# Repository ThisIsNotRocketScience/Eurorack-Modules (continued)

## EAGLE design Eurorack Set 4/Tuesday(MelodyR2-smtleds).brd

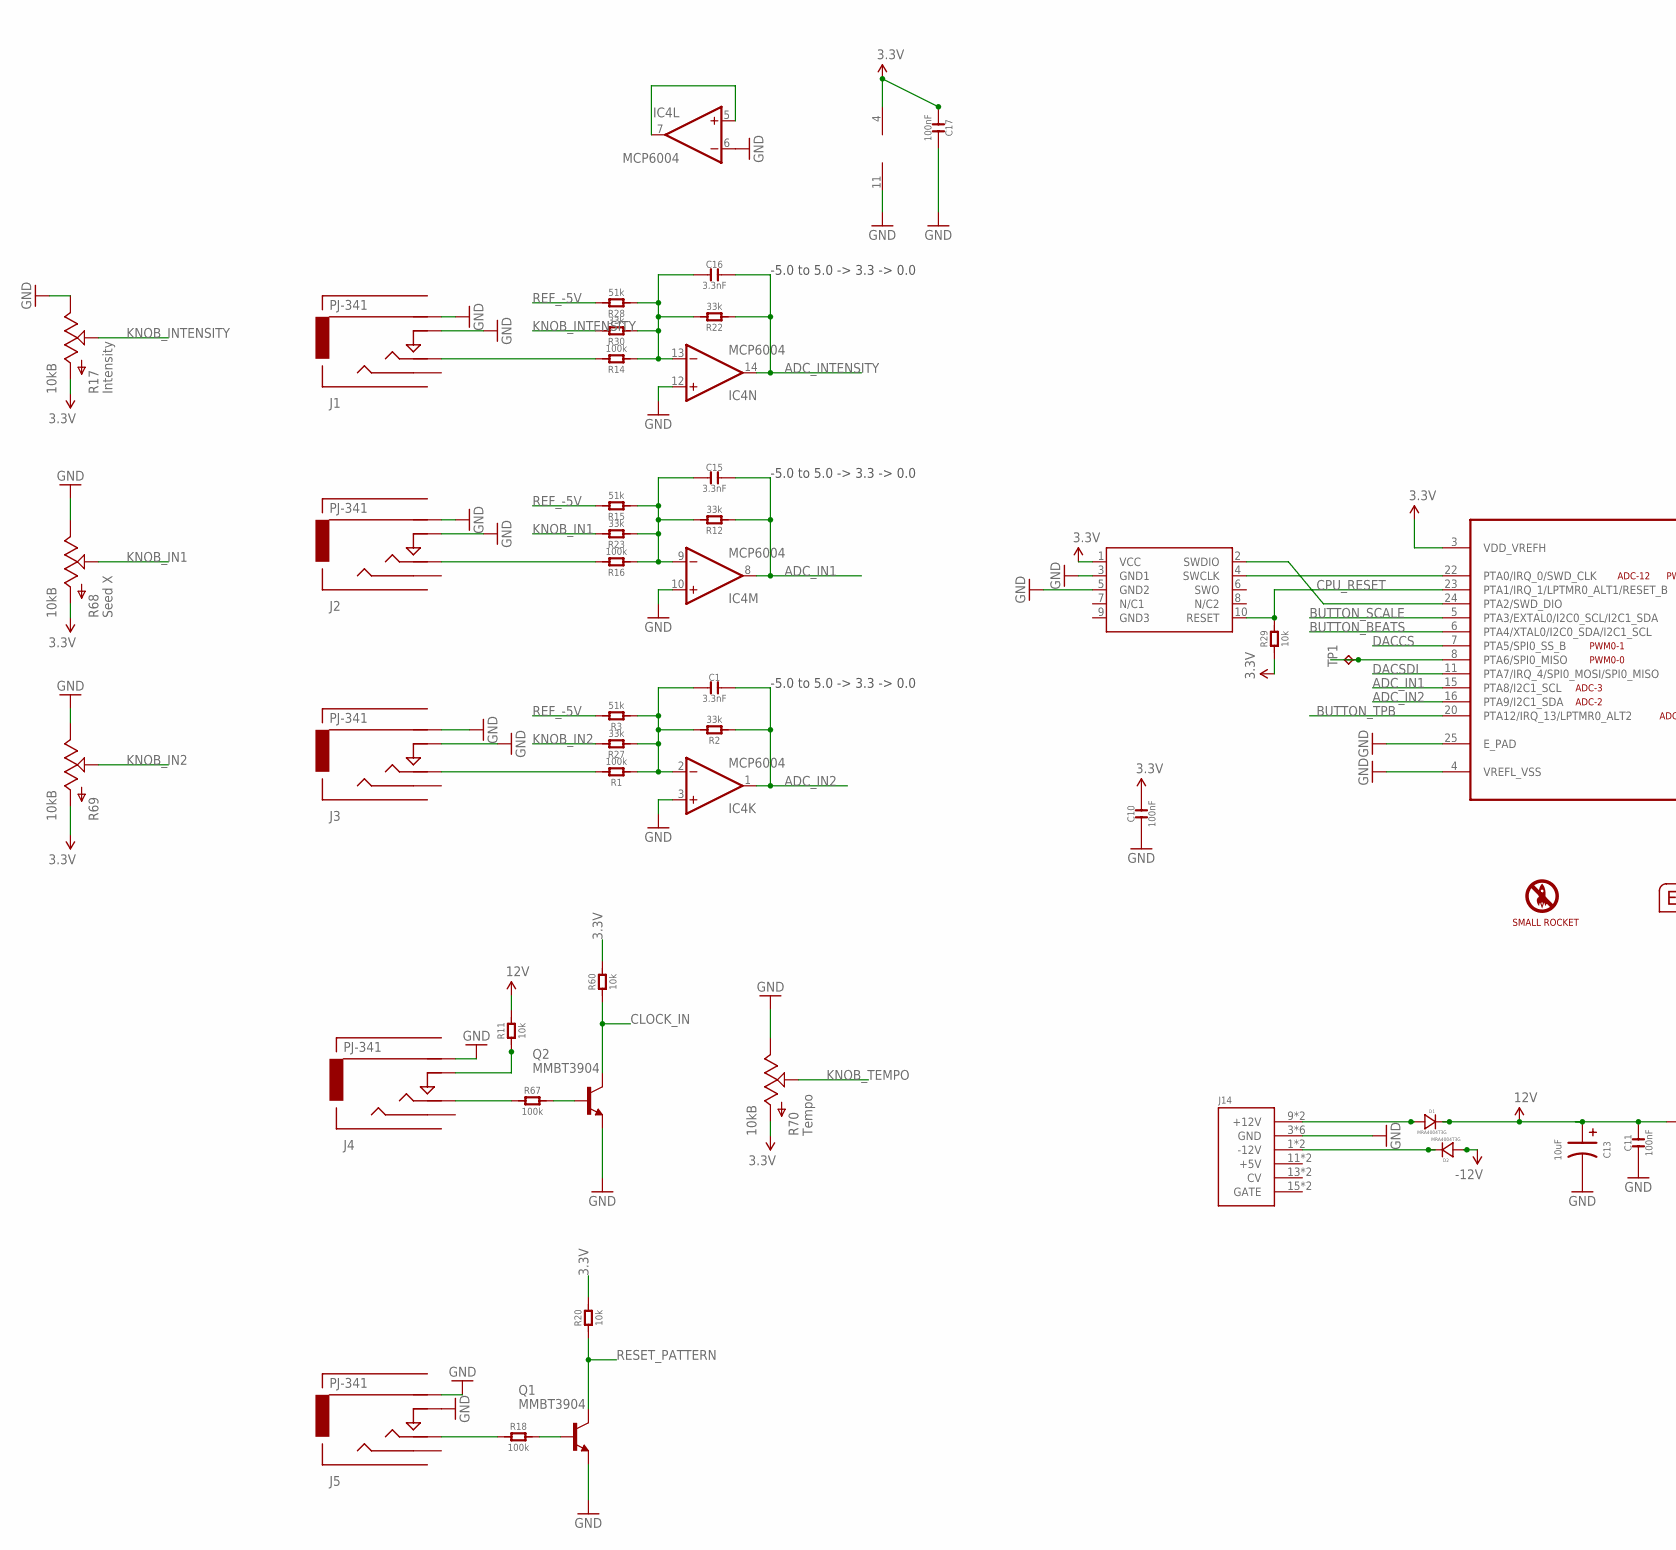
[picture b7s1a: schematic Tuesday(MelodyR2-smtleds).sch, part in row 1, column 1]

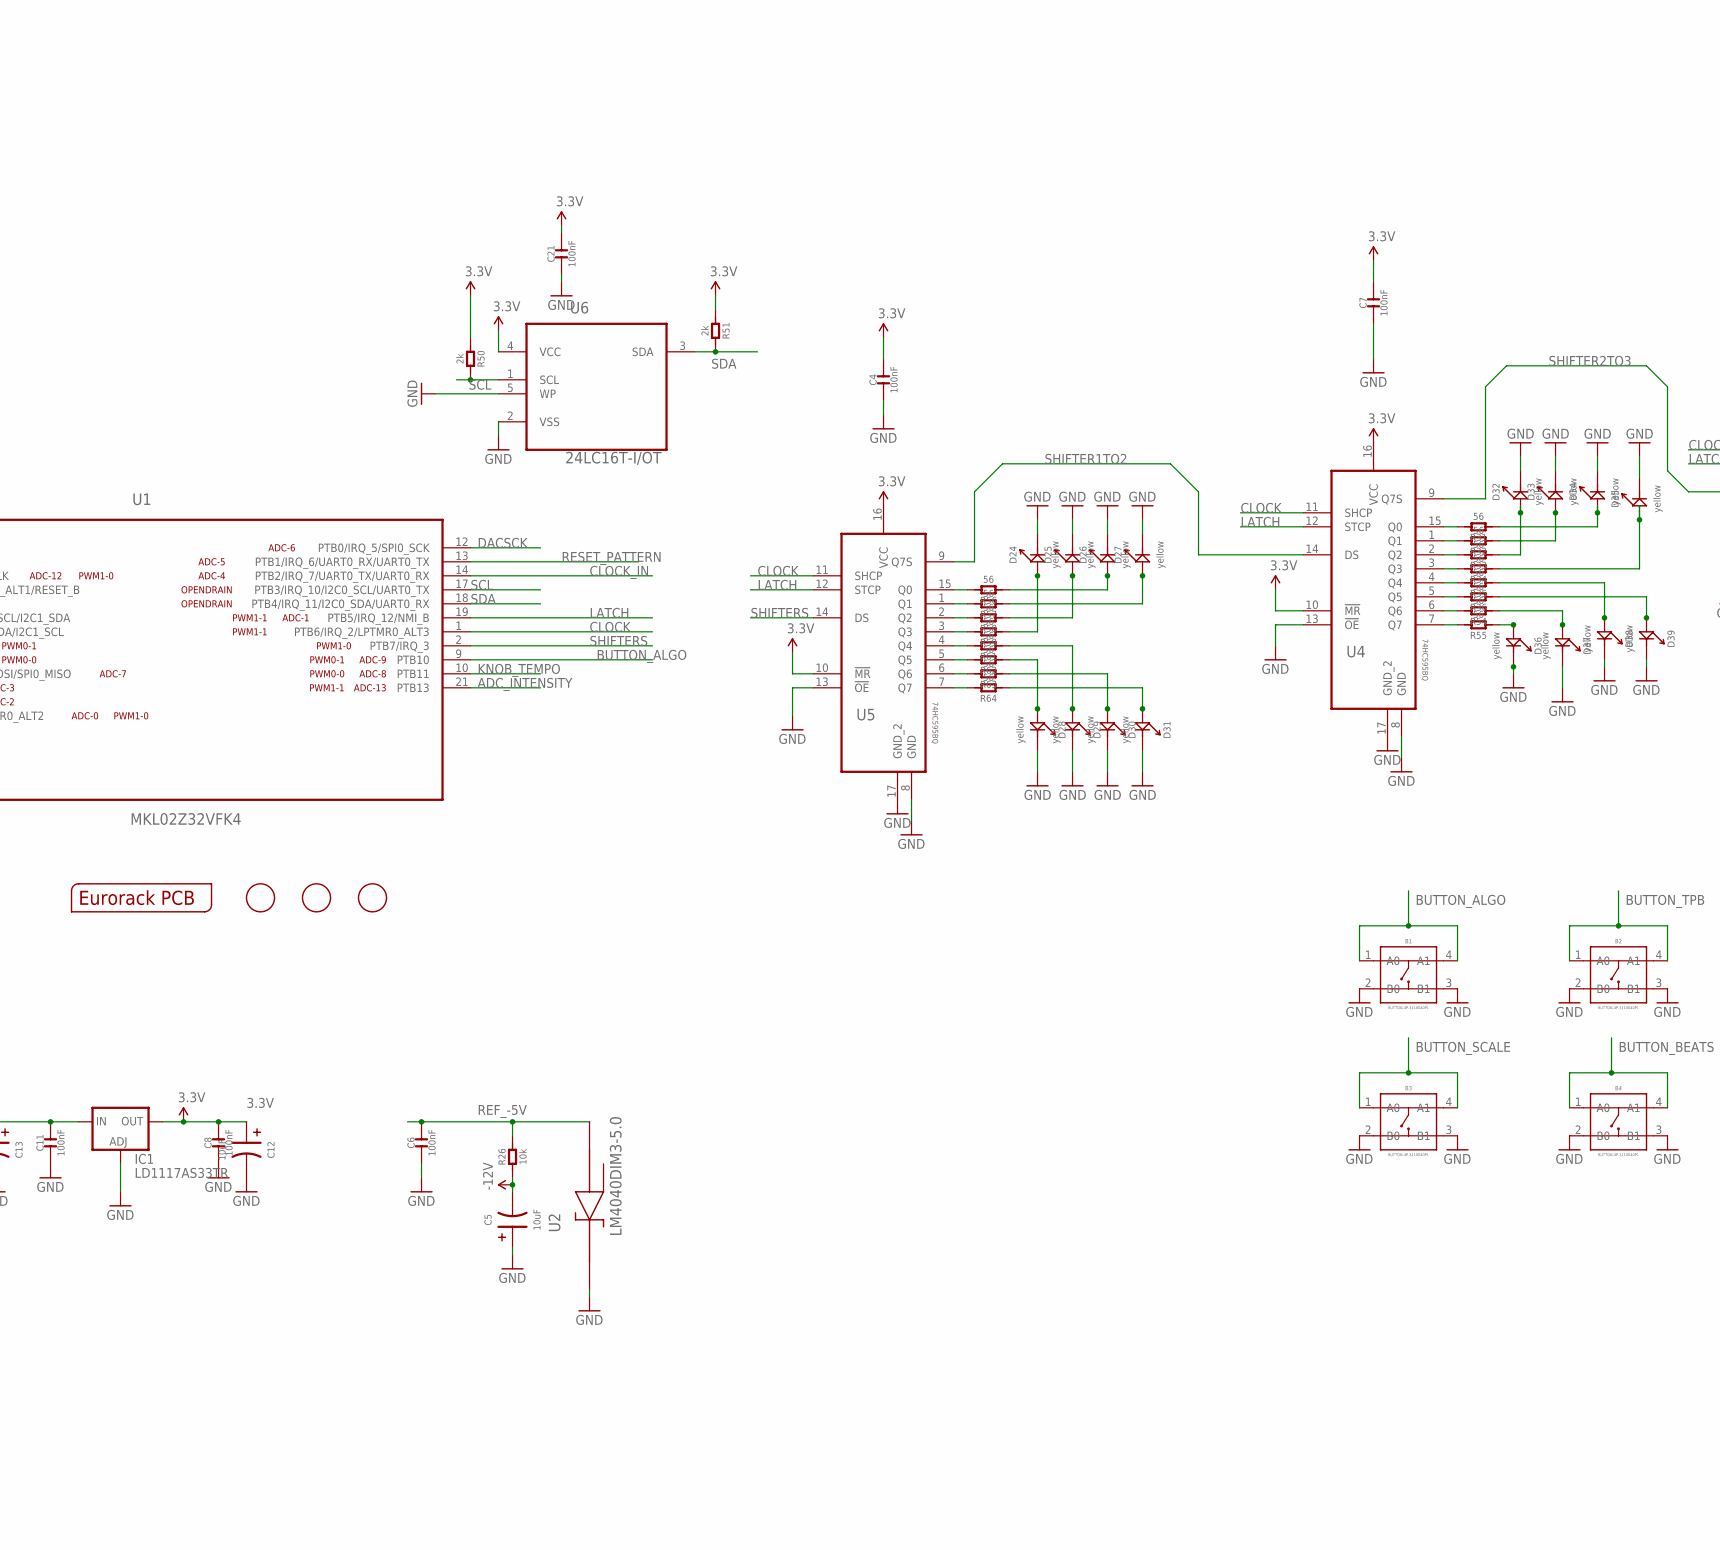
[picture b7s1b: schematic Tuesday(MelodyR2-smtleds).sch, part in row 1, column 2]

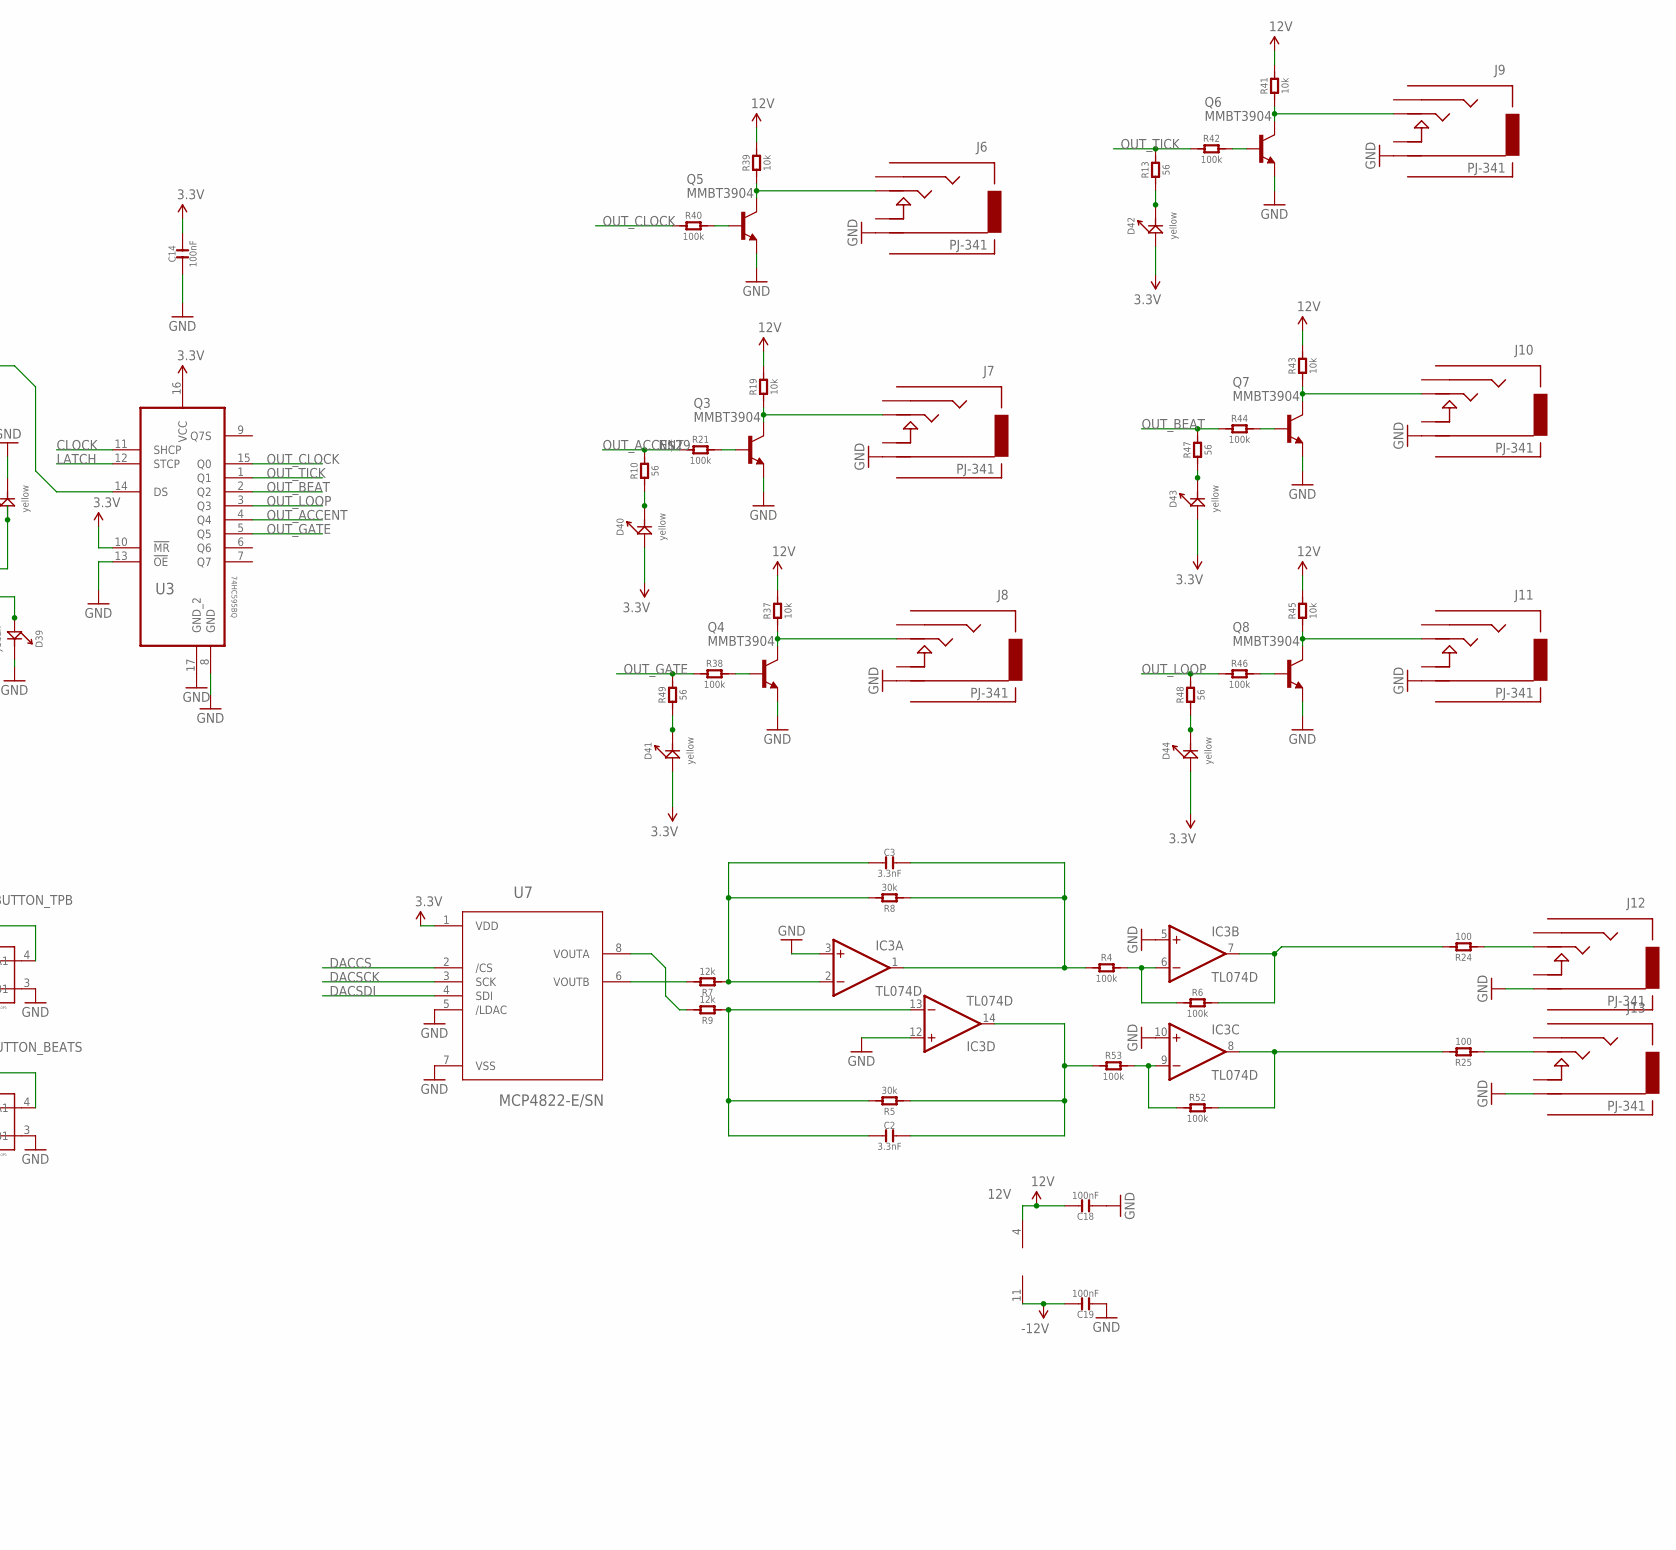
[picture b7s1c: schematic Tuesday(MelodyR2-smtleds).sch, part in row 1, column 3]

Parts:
B1, B2, B3, B4: BUTTON-4P-3110040P1; 4P-6.0X6.0X5.0H
C1, C2, C3, C15, C16: 3.3nF; C0603
C4, C7, C8, C10, C11, C14, C17, C18, C19, C21: 100nF; C0603; MPN MC0603F104Z160CT
C5, C12, C13: 10uF; AVX-A; MPN TAJB106K020RNJ
C6: 100nF; C0603; MPN 06035C104KAT2A
D1, D2: MRA4004T3G; DO-214AC; MPN US1G-E3/5AT
D24, D25, D26, D27, D28, D29, D30, D31, D32, D33, D34, D35, D36, D37, D38, D39, D40, D41, D42, D43, D44: yellow; LED0603
FID1, FID2, FID3: FIDUCIAL; FIDUCIAL_1MM
IC1: LD1117AS33TR; SOT223; MPN LD1117AS33TR
IC3: TL074D; SO14; MPN TL074CD
IC4: MCP6004; SO14; MPN MCP6004-I/SL.
J1, J2, J3, J4, J5: PJ-341; 3.5MM-JACK-SWITCH-13MM-INPUT
J6, J7, J8, J9, J10, J11, J12, J13: PJ-341; 3.5MM-JACK-SWITCH-13MM-OUTPUT
J14: POWER; POWER_16
OUTLINE: EURORACK_PCB12HP; EURORACK12HPPCB
PRETTY1: SMALLROCKET
Q1, Q2, Q3, Q4, Q5, Q6, Q7, Q8: MMBT3904; SOT23-BEC; MPN PMBT3904,215
R1, R4, R6, R14, R16, R18, R21, R38, R40, R42, R44, R46, R52, R53, R67: 100k; R0603
R2, R12, R22, R23, R27, R30: 33k; R0603
R3, R15, R28: 51k; R0603
R5, R8: 30k; R0603
R7, R9: 12k; R0603
R10, R13, R31, R32, R33, R34, R35, R36, R47, R48, R49, R54, R55, R56, R57, R58, R59, R61, R62, R63, R64: 56; R0603
R11, R19, R20, R26, R29, R37, R39, R41, R43, R45, R60: 10k; R0603
R17, R68, R69, R70: 10kB; OG-POTS_ALPS_POT_VERTICAL
R24, R25: 100; R0603
R50, R51: 2k; R0603
SWD1: CORTEX_SWD; M50-3600542
TP1: TPB1,27; B1,27
U1: MKL02Z32VFK4; QFN50P400X400X100-25N
U2: LM4040DIM3-5.0; SOT95P237X112-3N
U3, U4, U5: 74HC595BQ; QFN50P250X350X100-17N
U6: 24LC16T-I/OT; SOT95P290X145-5N; MPN 24LC00T-I/OT
U7: MCP4822-E/SN; SOIC8-N_MC

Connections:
3.3V: C4.2, C7.2, C8.2, C10.2, C12.+ (1), C14.2, C17.1, C21.2, D40.+, D41.+, D42.+, D43.+, D44.+, IC1.2 (OUT), IC1.4 (OUT), IC4.4 (V+), R17.P$3 (A), R20.2, R29.1, R50.1, R51.1, R60.2, R68.P$3 (A), R69.P$3 (A), R70.P$3 (A), SWD1.1 (VCC), U1.3 (VDD_VREFH), U3.10 (!MR), U3.16 (VCC), U4.10 (!MR), U4.16 (VCC), U5.10 (!MR), U5.16 (VCC), U6.4 (VCC), U7.1 (VDD)
12V: C11.2, C13.+ (1), C18.2, D1.2 (-), IC1.3 (IN), IC3.4 (V+), R11.2, R19.2, R37.2, R39.2, R41.2, R43.2, R45.2
-12V: C5.- (2), C19.2, D2.1 (+), IC3.11 (V-), R26.1
ADC_IN1: C15.2, IC4.8 (OUT), R12.1, U1.15 (PTA8/I2C1_SCL)
ADC_IN2: C1.2, IC4.1 (OUT), R2.1, U1.16 (PTA9/I2C1_SDA)
ADC_INTENSITY: C16.2, IC4.14 (OUT), R22.1, U1.21 (PTB13)
BUTTON_ALGO: B1.1 (A0), B1.4 (A1), U1.9 (PTB10)
BUTTON_BEATS: B4.1 (A0), B4.4 (A1), U1.6 (PTA4/XTAL0/I2C0_SDA/I2C1_SCL)
BUTTON_SCALE: B3.1 (A0), B3.4 (A1), U1.5 (PTA3/EXTAL0/I2C0_SCL/I2C1_SDA)
BUTTON_TPB: B2.1 (A0), B2.4 (A1), U1.20 (PTA12/IRQ_13/LPTMR0_ALT2)
CLOCK: U1.1 (PTB6/IRQ_2/LPTMR0_ALT3), U3.11 (SHCP), U4.11 (SHCP), U5.11 (SHCP)
CLOCK_IN: Q2.C, R60.1, U1.14 (PTB2/IRQ_7/UART0_TX/UART0_RX)
CPU_RESET: R29.2, SWD1.10 (RESET), U1.23 (PTA1/IRQ_1/LPTMR0_ALT1/RESET_B)
D21: D43.-, R47.1
DACCS: U1.7 (PTA5/SPI0_SS_B), U7.2 (/CS)
DACSCK: U1.12 (PTB0/IRQ_5/SPI0_SCK), U7.3 (SCK)
DACSDI: U1.11 (PTA7/IRQ_4/SPI0_MOSI/SPI0_MISO), U7.4 (SDI)
GND: B1.2 (B0), B1.3 (B1), B2.2 (B0), B2.3 (B1), B3.2 (B0), B3.3 (B1), B4.2 (B0), B4.3 (B1), C4.1, C5.+ (1), C6.1, C7.1, C8.1, C10.1, C11.1, C12.- (2), C13.- (2), C14.1, C17.2, C18.1, C19.1, C21.1, D24.-, D25.-, D26.-, D27.-, D28.-, D29.-, D30.-, D31.-, D32.-, D33.-, D34.-, D35.-, D36.-, D37.-, D38.-, D39.-, IC1.1 (ADJ), IC3.3 (+IN), IC3.5 (+IN), IC3.10 (+IN), IC3.12 (+IN), IC4.3 (+IN), IC4.6 (-IN), IC4.10 (+IN), IC4.11 (V-), IC4.12 (+IN), J1.RING@3 (RING), J1.SWITCH@3 (SWITCH), J2.RING@3 (RING), J2.SWITCH@3 (SWITCH), J3.RING@3 (RING), J3.SWITCH@3 (SWITCH), J4.RING@3 (RING), J5.RING@3 (RING), J5.SWITCH@3 (SWITCH), J6.RING@3 (RING), J7.RING@3 (RING), J8.RING@3 (RING), J9.RING@3 (RING), J10.RING@3 (RING), J11.RING@3 (RING), J12.RING@3 (RING), J13.RING@3 (RING), J14.3 (GND), J14.4 (GND), J14.5 (GND), J14.6 (GND), J14.7 (GND), J14.8 (GND), Q1.E, Q2.E, Q3.E, Q4.E, Q5.E, Q6.E, Q7.E, Q8.E, R17.P$1 (E), R68.P$1 (E), R69.P$1 (E), R70.P$1 (E), SWD1.3 (GND1), SWD1.5 (GND2), U1.4 (VREFL_VSS), U1.25 (E_PAD), U2.1 (CATHODE), U3.8 (GND), U3.13 (!OE), U3.17 (GND_2), U4.8 (GND), U4.13 (!OE), U4.17 (GND_2), U5.8 (GND), U5.13 (!OE), U5.17 (GND_2), U6.2 (VSS), U6.5 (WP), U7.5 (/LDAC), U7.7 (VSS)
KNOB_IN1: R23.2, R68.P$2 (S)
KNOB_IN2: R27.2, R69.P$2 (S)
KNOB_INTENSITY: R17.P$2 (S), R30.2
KNOB_TEMPO: R70.P$2 (S), U1.10 (PTB11)
LATCH: U1.19 (PTB5/IRQ_12/NMI_B), U3.12 (STCP), U4.12 (STCP), U5.12 (STCP)
unnamed: R32.2, U4.1 (Q1)
unnamed: IC3.6 (-IN), R4.2, R6.1
unnamed: J2.TIP@3 (TIP), R16.2
unnamed: C15.1, IC4.9 (-IN), R12.2, R15.1, R16.1, R23.1
unnamed: R9.2, U7.8 (VOUTA)
unnamed: J3.TIP@3 (TIP), R1.2
unnamed: R7.2, U7.6 (VOUTB)
unnamed: C1.1, IC4.2 (-IN), R1.1, R2.2, R3.1, R27.1
unnamed: C2.1, IC3.13 (-IN), R5.2, R9.1
unnamed: C3.1, IC3.2 (-IN), R7.1, R8.2
unnamed: D42.-, R13.1
unnamed: D1.1 (+), J14.9 (+12V), J14.10 (+12V)
unnamed: IC3.7 (OUT), R6.2, R24.2
unnamed: Q1.B, R18.2
unnamed: J5.TIP@3 (TIP), R18.1
unnamed: IC3.9 (-IN), R52.1, R53.2
unnamed: C3.2, IC3.1 (OUT), R4.1, R8.1
unnamed: R33.2, U4.2 (Q2)
unnamed: J13.TIP@3 (TIP), R25.1
unnamed: J12.TIP@3 (TIP), R24.1
unnamed: D40.-, R10.1
unnamed: C2.2, IC3.14 (OUT), R5.1, R53.1
unnamed: Q3.B, R21.2
unnamed: R34.2, U4.3 (Q3)
unnamed: R35.2, U4.4 (Q4)
unnamed: D28.+, R62.1
unnamed: J7.TIP@3 (TIP), Q3.C, R19.1
unnamed: R36.2, U4.5 (Q5)
unnamed: R54.2, U4.6 (Q6)
unnamed: D29.+, R61.1
unnamed: J1.TIP@3 (TIP), R14.2
unnamed: C16.1, IC4.13 (-IN), R14.1, R22.2, R28.1, R30.1
unnamed: R55.2, U4.7 (Q7)
unnamed: R31.2, U4.15 (Q0)
unnamed: R56.2, U5.15 (Q0)
unnamed: R57.2, U5.1 (Q1)
unnamed: R58.2, U5.2 (Q2)
unnamed: R59.2, U5.3 (Q3)
unnamed: R61.2, U5.4 (Q4)
unnamed: R62.2, U5.5 (Q5)
unnamed: J4.TIP@3 (TIP), R67.1
unnamed: D41.-, R49.1
unnamed: D44.-, R48.1
unnamed: R63.2, U5.6 (Q6)
unnamed: R64.2, U5.7 (Q7)
unnamed: Q4.B, R38.2
unnamed: J8.TIP@3 (TIP), Q4.C, R37.1
unnamed: Q5.B, R40.2
unnamed: J6.TIP@3 (TIP), Q5.C, R39.1
unnamed: Q6.B, R42.2
unnamed: D2.2 (-), J14.1 (-12V), J14.2 (-12V)
unnamed: J9.TIP@3 (TIP), Q6.C, R41.1
unnamed: Q2.B, R67.2
unnamed: Q7.B, R44.2
unnamed: J10.TIP@3 (TIP), Q7.C, R43.1
unnamed: Q8.B, R46.2
unnamed: J11.TIP@3 (TIP), Q8.C, R45.1
unnamed: D27.+, R57.1
unnamed: D26.+, R56.1
unnamed: D25.+, R58.1
unnamed: D24.+, R59.1
unnamed: D30.+, R63.1
unnamed: D31.+, R64.1
unnamed: D32.+, R33.1
unnamed: D33.+, R32.1
unnamed: D34.+, R31.1
unnamed: D35.+, R34.1
unnamed: D36.+, R55.1
unnamed: D37.+, R54.1
unnamed: D38.+, R35.1
unnamed: D39.+, R36.1
unnamed: IC3.8 (OUT), R25.2, R52.2
unnamed: J4.SWITCH@3 (SWITCH), R11.1
unnamed: IC4.5 (+IN), IC4.7 (OUT)
OUT_ACCENT: R10.2, R21.1, U3.4 (Q4)
OUT_BEAT: R44.1, R47.2, U3.2 (Q2)
OUT_CLOCK: R40.1, U3.15 (Q0)
OUT_GATE: R38.1, R49.2, U3.5 (Q5)
OUT_LOOP: R46.1, R48.2, U3.3 (Q3)
OUT_TICK: R13.2, R42.1, U3.1 (Q1)
PTA6: TP1.TP, U1.8 (PTA6/SPI0_MISO)
REF_-5V: C6.2, R3.2, R15.2, R26.2, R28.2, U2.2 (ANODE)
RESET_PATTERN: Q1.C, R20.1, U1.13 (PTB1/IRQ_6/UART0_RX/UART0_TX)
SCL: R50.2, U1.17 (PTB3/IRQ_10/I2C0_SCL/UART0_TX), U6.1 (SCL)
SDA: R51.2, U1.18 (PTB4/IRQ_11/I2C0_SDA/UART0_RX), U6.3 (SDA)
SHIFTER1TO2: U4.14 (DS), U5.9 (Q7S)
SHIFTER2TO3: U3.14 (DS), U4.9 (Q7S)
SHIFTERS: U1.2 (PTB7/IRQ_3), U5.14 (DS)
SWD_CLK: SWD1.4 (SWCLK), U1.22 (PTA0/IRQ_0/SWD_CLK)
SWD_DIO: SWD1.2 (SWDIO), U1.24 (PTA2/SWD_DIO)

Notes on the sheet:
-5.0 to 5.0 -> 3.3 -> 0.0

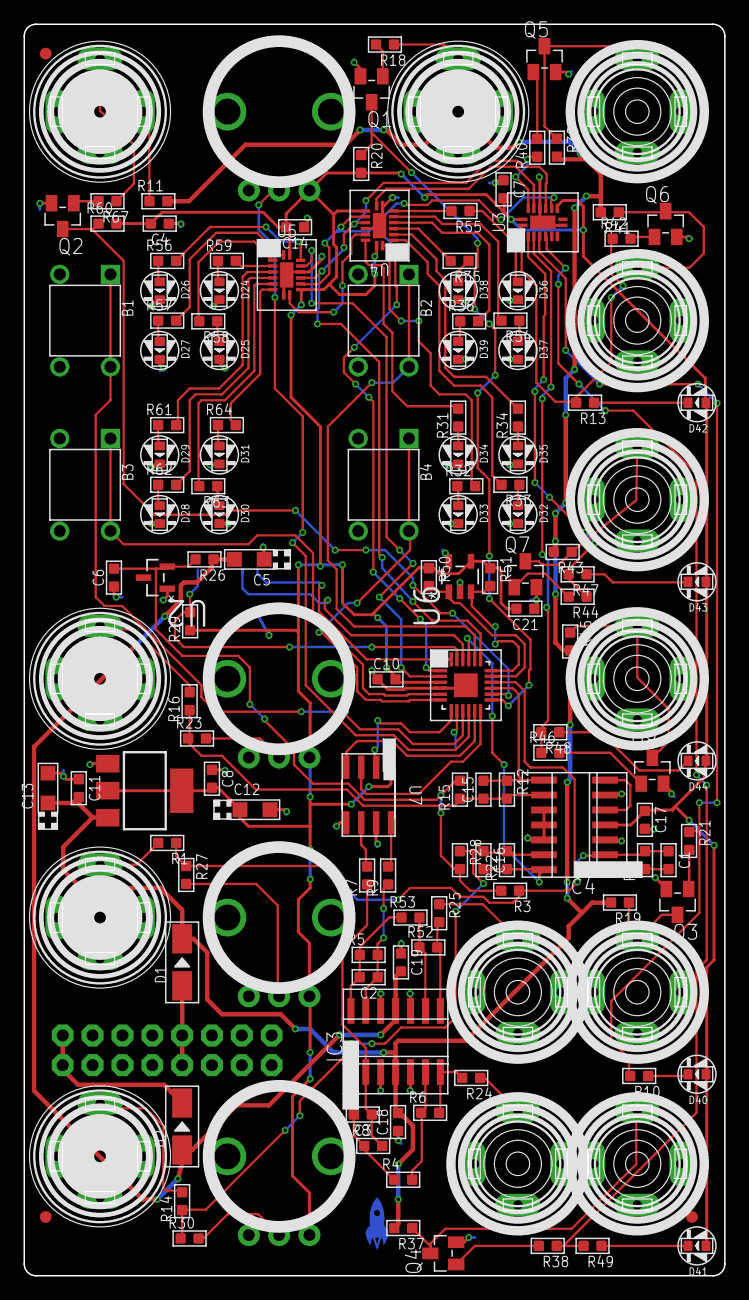
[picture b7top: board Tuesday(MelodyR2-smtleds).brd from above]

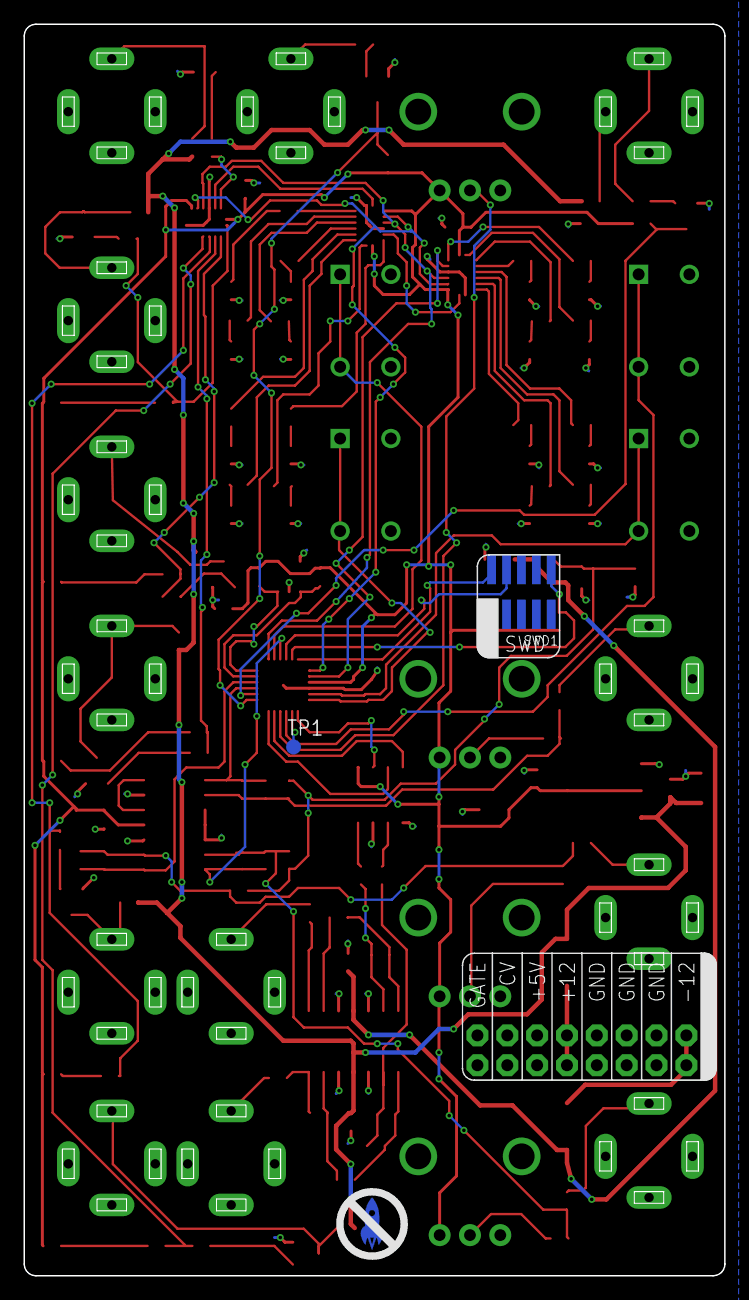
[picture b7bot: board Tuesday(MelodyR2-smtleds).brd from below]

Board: 2 copper layers, 59.6 x 106.5 mm, 153 parts (4 on the bottom side), 113 nets.
